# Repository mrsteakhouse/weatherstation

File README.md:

# Weather Station

A weather station equipped with a BME 280, a voltage sensor and any additional I2C device for monitoring temperature, humidity and air pressure in a room or outside.
It is designed to work with a ESP-01 in deep sleep, but any other ESP may work.
On 6 AA batteries it may run for half a year or longer.
PCB schematics can be found [here](https://github.com/mrsteakhouse/weatherstation-pcb).

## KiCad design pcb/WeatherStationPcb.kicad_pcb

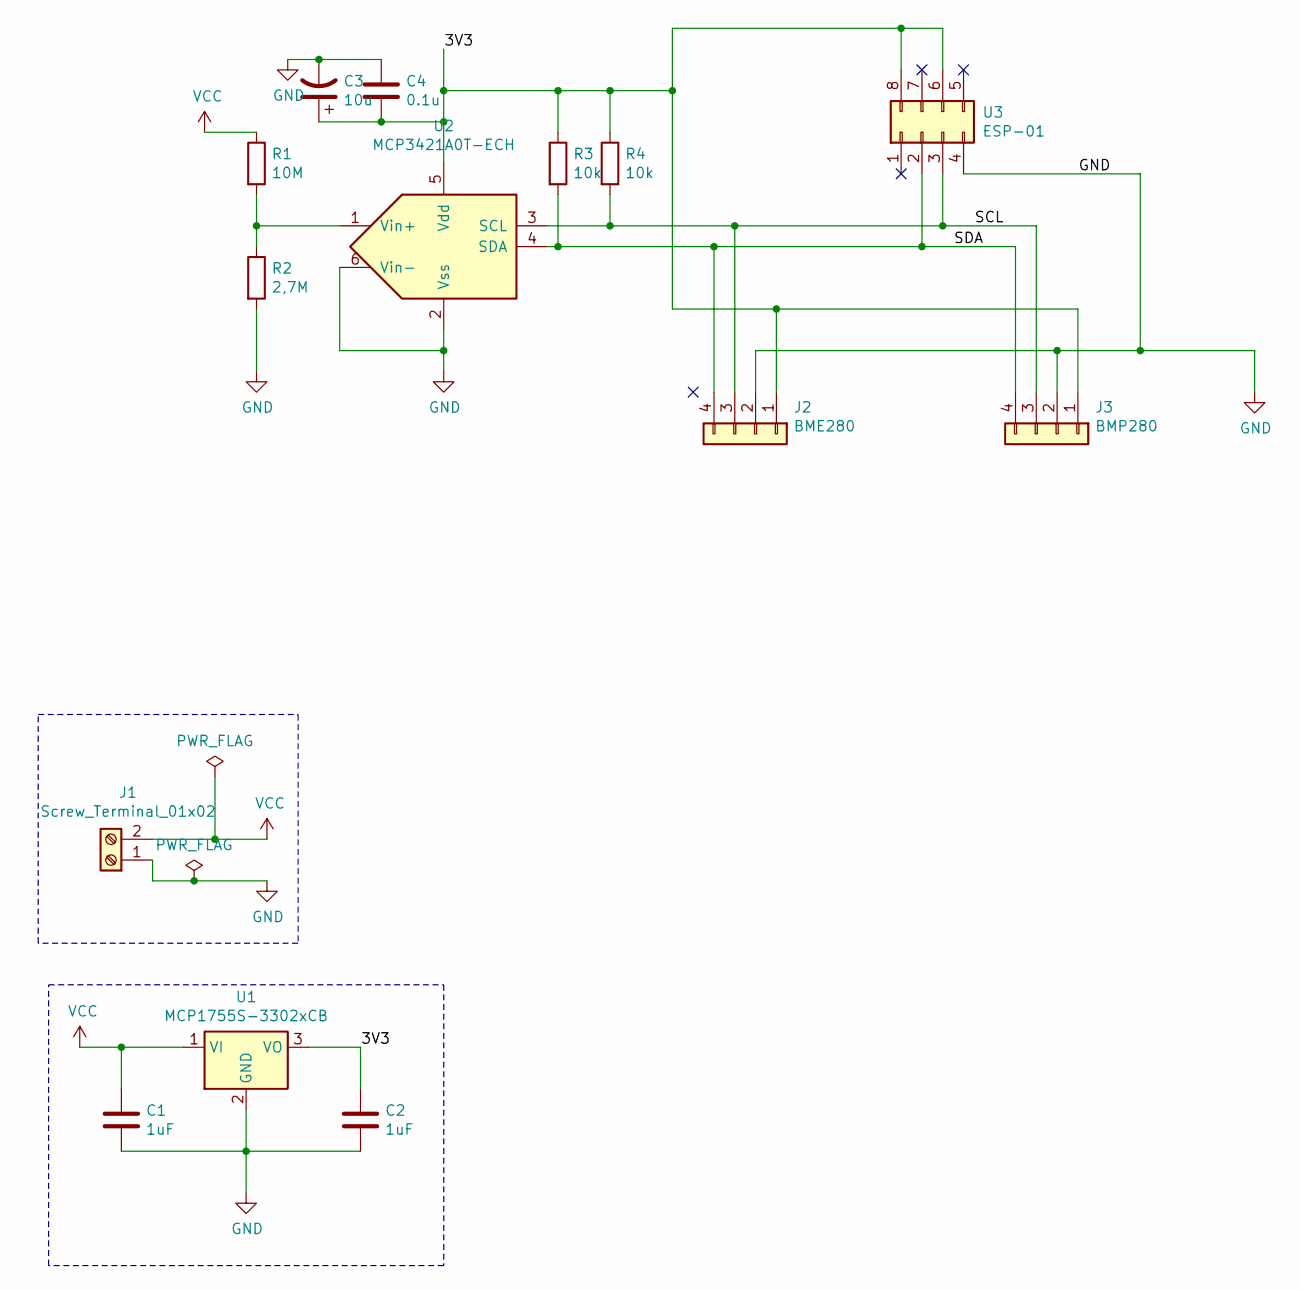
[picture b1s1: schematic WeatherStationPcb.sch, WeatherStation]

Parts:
C1, C2: 1uF; C_0805_2012Metric_Pad1.15x1.40mm_HandSolder
C3: 10u; CP_EIA-6032-28_Kemet-C_Pad2.25x2.35mm_HandSolder
C4: 0.1u; C_0805_2012Metric_Pad1.15x1.40mm_HandSolder
J1: Screw_Terminal_01x02; TerminalBlock_bornier-2_P5.08mm
J2: BME280; PinSocket_1x04_P2.54mm_Vertical
J3: BMP280; PinSocket_1x04_P2.54mm_Vertical
R1: 10M; R_0805_2012Metric_Pad1.15x1.40mm_HandSolder
R2: 2,7M; R_0805_2012Metric_Pad1.15x1.40mm_HandSolder
R3, R4: 10k; R_0805_2012Metric_Pad1.15x1.40mm_HandSolder
U1: MCP1755S-3302xCB; SOT-223
U2: MCP3421A0T-ECH; SOT-23-6_Handsoldering
U3: ESP-01

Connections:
/3V3: C2.1, C3.1, C4.1, J2.1, J3.1, R3.1, R4.1, U1.3 (VO), U2.5 (Vdd), U3.6 (CH_PD), U3.8 (VCC)
/SCL: J2.3, J3.3, R4.2, U2.3 (SCL), U3.3 (GPIO2)
/SDA: J2.4, J3.4, R3.2, U2.4 (SDA), U3.2 (GPIO0)
GND: C1.2, C2.2, C3.2, C4.2, J1.1, J2.2, J3.2, R2.2, U1.2 (GND), U2.2 (Vss), U2.6 (Vin-), U3.4 (GND)
unnamed: R1.2, R2.1, U2.1 (Vin+)
VCC: C1.1, J1.2, R1.1, U1.1 (VI)

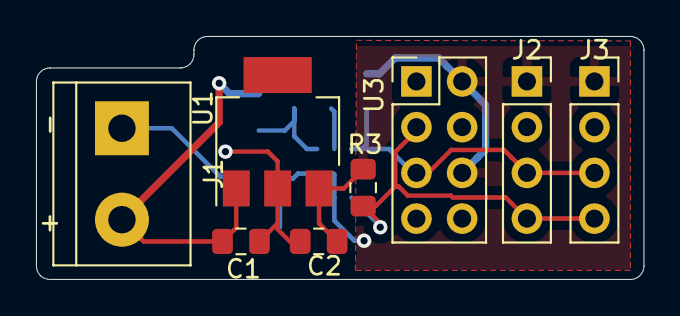
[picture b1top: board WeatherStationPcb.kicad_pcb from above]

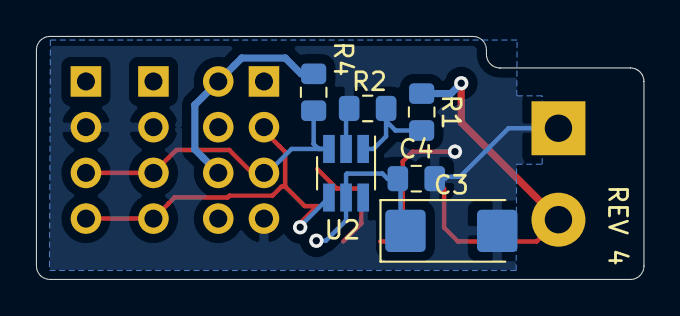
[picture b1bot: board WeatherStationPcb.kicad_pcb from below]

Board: 2 copper layers, 33.8 x 13.5 mm, 14 parts (6 on the bottom side), 6 nets.

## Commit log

2019-12-14 init
2020-05-16 feat(*): make it compilable again
2020-05-16 feat(WeatherStation.cpp): enable deep sleep
2020-05-16 feat(WeatherStation.cpp): restart when no wifi connection can be established
2020-05-16 feat(WeatherStation.cpp): adjust delays for the adapter to do its work
2020-05-16 feat(WeatherStation.cpp): use no cal that the wifi is able to connect after wakeup
2020-05-16 feat(WeatherStation.cpp): make delays more forgivable
2020-05-18 feat(WeatherStation.cpp): remove 3 digits to make it seconds
2020-05-20 feat(*): add pcb design
2020-05-20 chore(*): remove zip
2020-11-01 feat(homie): add mqtt message specification for weather station device
2020-11-01 feat(*): change value updating to mqtt publish
2020-11-01 feat(pcb): update pcb
2020-11-02 fix(homie-spec): use floats
2020-11-02 fix(*): change settings for better measurements
2020-11-02 fix(sleepTime): fix the sleep time
2020-11-02 fix(WeatherStation.cpp): fix typo
2020-11-02 fix(WeatherStation.cpp): take value from framework since sensor settings now deliver accurate values
2020-11-08 feat(pcb): update the pcb by adding voltage sensor
2020-11-14 feat(*): add support for battery levels
2020-11-14 feat(*): prepare for second weather station
2020-11-14 fix(homie.sh): fix host
2020-11-14 feat(WeatherStation.cpp): move device id to constant
2020-11-19 feat(*): make the voltage sensor more stable
2020-12-02 feat(homie.sh): add types
2020-12-23 fix(mqtt): remove pump node
2020-12-23 fix(*): remove libs and use forked repository
2020-12-23 feat(*): use libraries and make it work again
2020-12-23 feat(*): rename script
2020-12-23 feat(*): move pcb to own repository
2020-12-23 fix(*): some fixes
2020-12-23 refactor(*): move code into separate classes
